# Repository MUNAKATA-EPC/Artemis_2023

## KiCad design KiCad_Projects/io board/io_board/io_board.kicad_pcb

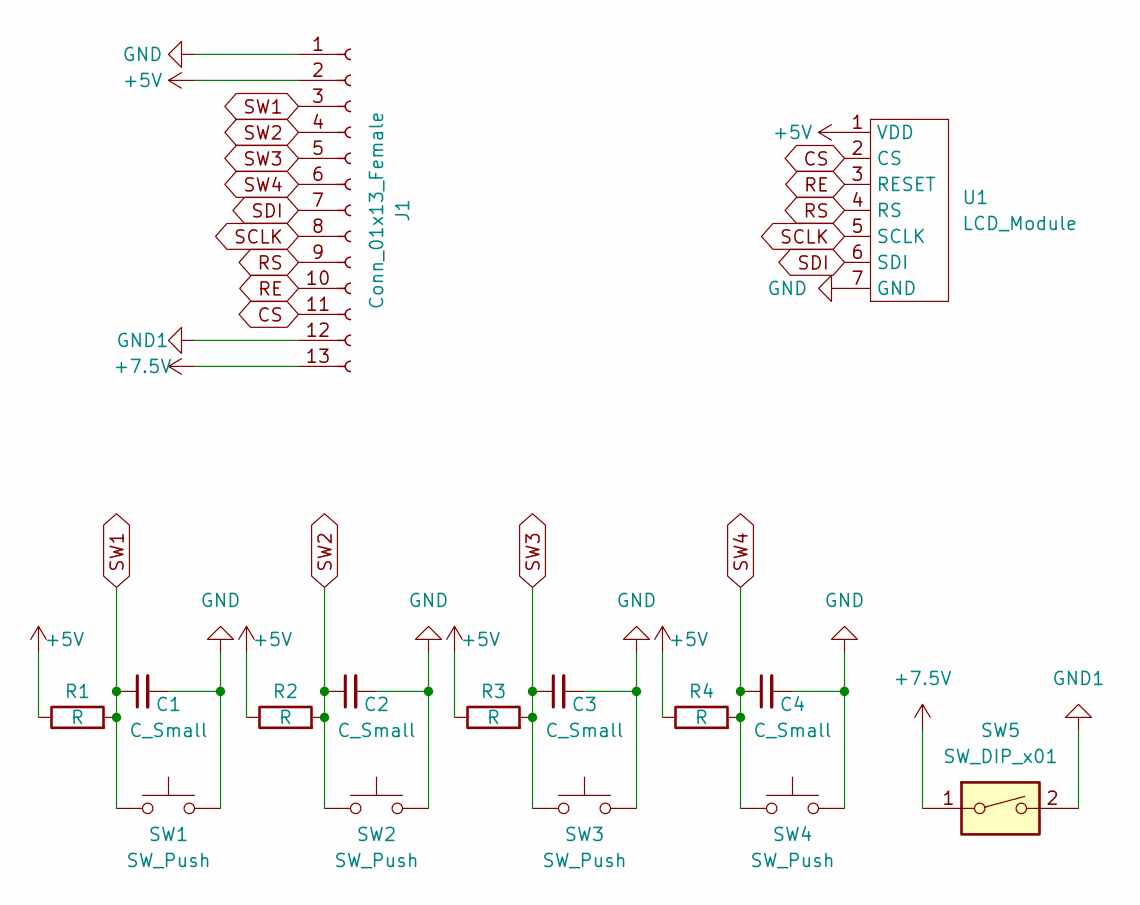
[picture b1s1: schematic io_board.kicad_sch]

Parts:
C1, C2, C3, C4: C_Small
J1: Conn_01x13_Female
R1, R2, R3, R4: R
SW1, SW2, SW3, SW4: SW_Push
SW5: SW_DIP_x01
U1: LCD_Module

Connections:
+5V: J1.2, R1.1, R2.1, R3.1, R4.1, U1.1 (VDD)
+7.5V: J1.13, SW5.1
CS: J1.11, U1.2 (CS)
GND: C1.2, C2.2, C3.2, C4.2, J1.1, SW1.2, SW2.2, SW3.2, SW4.2, U1.7 (GND)
GND1: J1.12, SW5.2
RE: J1.10, U1.3 (RESET)
RS: J1.9, U1.4 (RS)
SCLK: J1.8, U1.5 (SCLK)
SDI: J1.7, U1.6 (SDI)
SW1: C1.1, J1.3, R1.2, SW1.1
SW2: C2.1, J1.4, R2.2, SW2.1
SW3: C3.1, J1.5, R3.2, SW3.1
SW4: C4.1, J1.6, R4.2, SW4.1

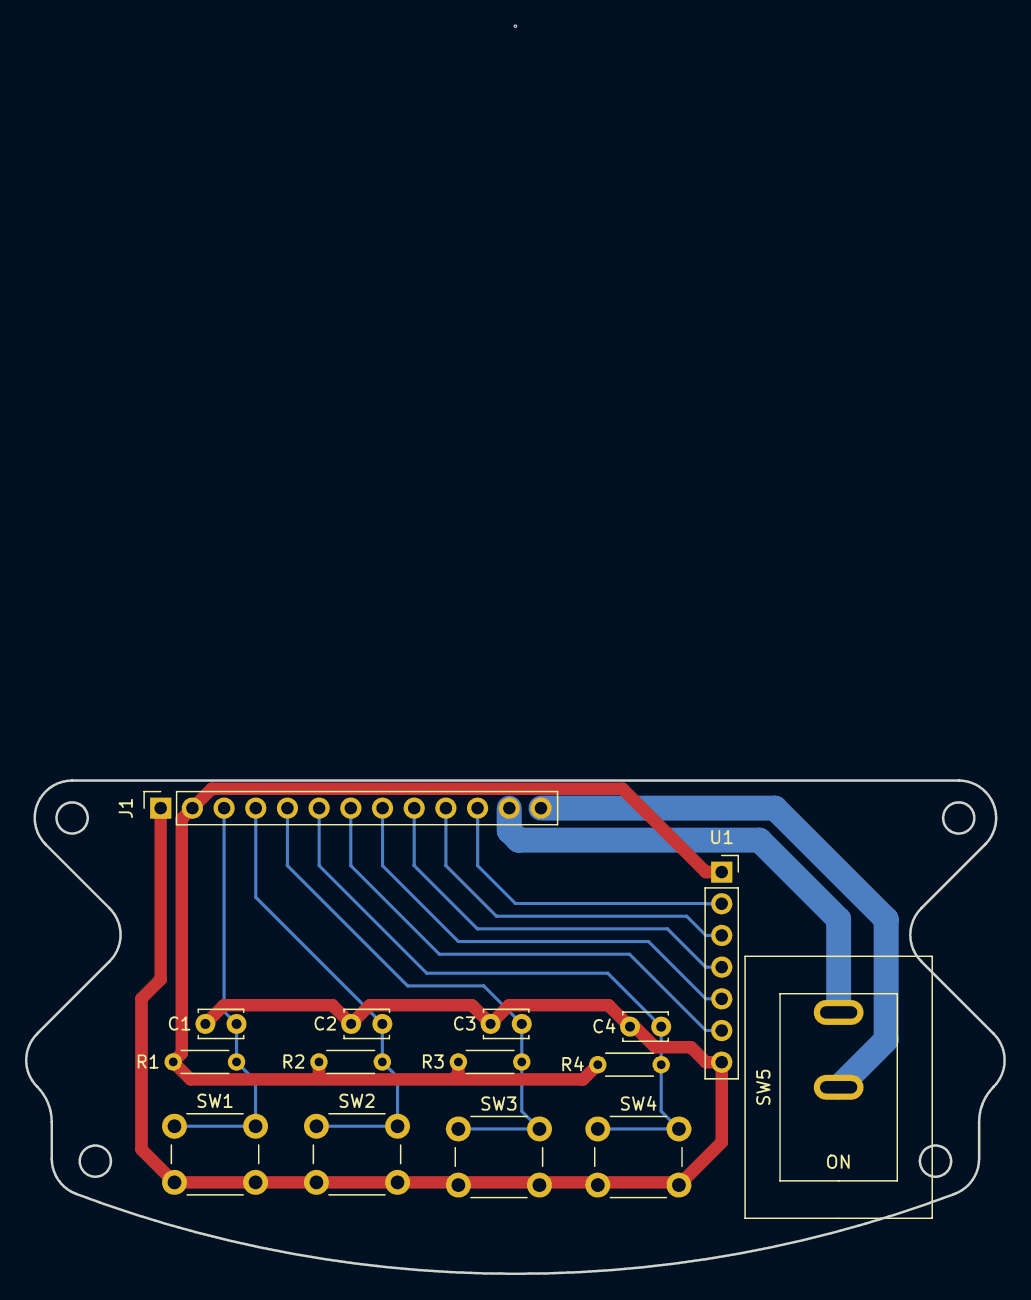
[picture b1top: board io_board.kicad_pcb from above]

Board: 2 copper layers, 78.4 x 39.5 mm, 15 parts (0 on the bottom side), 13 nets.

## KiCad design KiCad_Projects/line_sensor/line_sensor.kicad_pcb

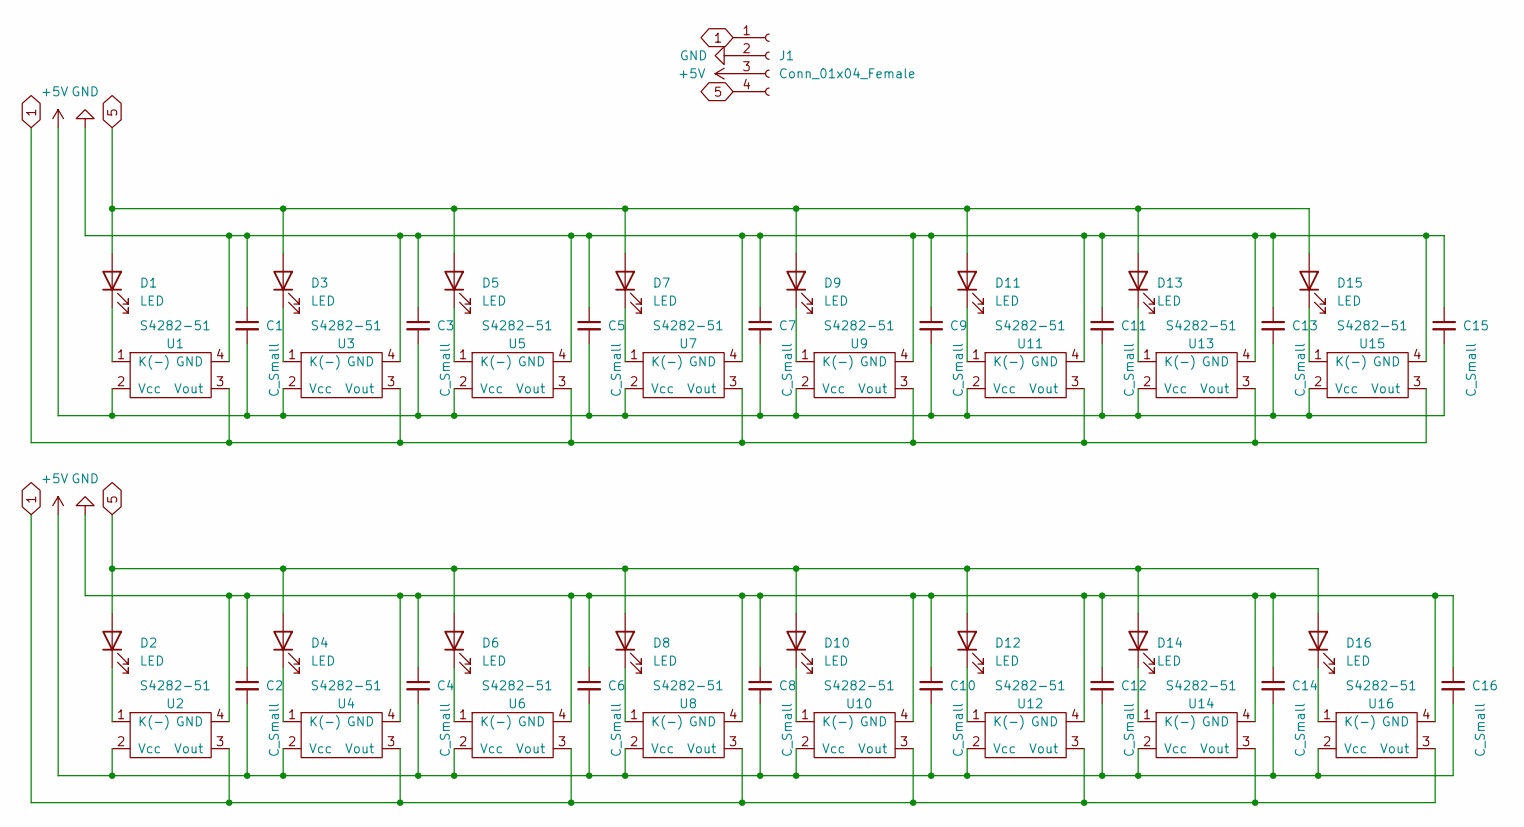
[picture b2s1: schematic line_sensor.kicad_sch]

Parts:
C1, C2, C3, C4, C5, C6, C7, C8, C9, C10, C11, C12, C13, C14, C15, C16: C_Small; C_Disc_D3.8mm_W2.6mm_P2.50mm
D1, D2, D3, D4, D5, D6, D7, D8, D9, D10, D11, D12, D13, D14, D15, D16: LED; LED_D3.0mm_Clear
J1: Conn_01x04_Female; JST_XH_B4B-XH-A_1x04_P2.50mm_Vertical
U1, U2, U3, U4, U5, U6, U7, U8, U9, U10, U11, U12, U13, U14, U15, U16: S4282-51; Line_sennsor

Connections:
1: J1.1, U1.3 (Vout), U2.3 (Vout), U3.3 (Vout), U4.3 (Vout), U5.3 (Vout), U6.3 (Vout), U7.3 (Vout), U8.3 (Vout), U9.3 (Vout), U10.3 (Vout), U11.3 (Vout), U12.3 (Vout), U13.3 (Vout), U14.3 (Vout), U15.3 (Vout), U16.3 (Vout)
5: D1.2 (A), D2.2 (A), D3.2 (A), D4.2 (A), D5.2 (A), D6.2 (A), D7.2 (A), D8.2 (A), D9.2 (A), D10.2 (A), D11.2 (A), D12.2 (A), D13.2 (A), D14.2 (A), D15.2 (A), D16.2 (A), J1.4
+5V: C1.2, C2.2, C3.2, C4.2, C5.2, C6.2, C7.2, C8.2, C9.2, C10.2, C11.2, C12.2, C13.2, C14.2, C15.2, C16.2, J1.3, U1.2 (Vcc), U2.2 (Vcc), U3.2 (Vcc), U4.2 (Vcc), U5.2 (Vcc), U6.2 (Vcc), U7.2 (Vcc), U8.2 (Vcc), U9.2 (Vcc), U10.2 (Vcc), U11.2 (Vcc), U12.2 (Vcc), U13.2 (Vcc), U14.2 (Vcc), U15.2 (Vcc), U16.2 (Vcc)
GND: C1.1, C2.1, C3.1, C4.1, C5.1, C6.1, C7.1, C8.1, C9.1, C10.1, C11.1, C12.1, C13.1, C14.1, C15.1, C16.1, J1.2, U1.4 (GND), U2.4 (GND), U3.4 (GND), U4.4 (GND), U5.4 (GND), U6.4 (GND), U7.4 (GND), U8.4 (GND), U9.4 (GND), U10.4 (GND), U11.4 (GND), U12.4 (GND), U13.4 (GND), U14.4 (GND), U15.4 (GND), U16.4 (GND)
unnamed: D1.1 (K), U1.1 (K(-))
unnamed: D2.1 (K), U2.1 (K(-))
unnamed: D3.1 (K), U3.1 (K(-))
unnamed: D4.1 (K), U4.1 (K(-))
unnamed: D5.1 (K), U5.1 (K(-))
unnamed: D6.1 (K), U6.1 (K(-))
unnamed: D7.1 (K), U7.1 (K(-))
unnamed: D8.1 (K), U8.1 (K(-))
unnamed: D9.1 (K), U9.1 (K(-))
unnamed: D10.1 (K), U10.1 (K(-))
unnamed: D11.1 (K), U11.1 (K(-))
unnamed: D12.1 (K), U12.1 (K(-))
unnamed: D13.1 (K), U13.1 (K(-))
unnamed: D14.1 (K), U14.1 (K(-))
unnamed: D15.1 (K), U15.1 (K(-))
unnamed: D16.1 (K), U16.1 (K(-))

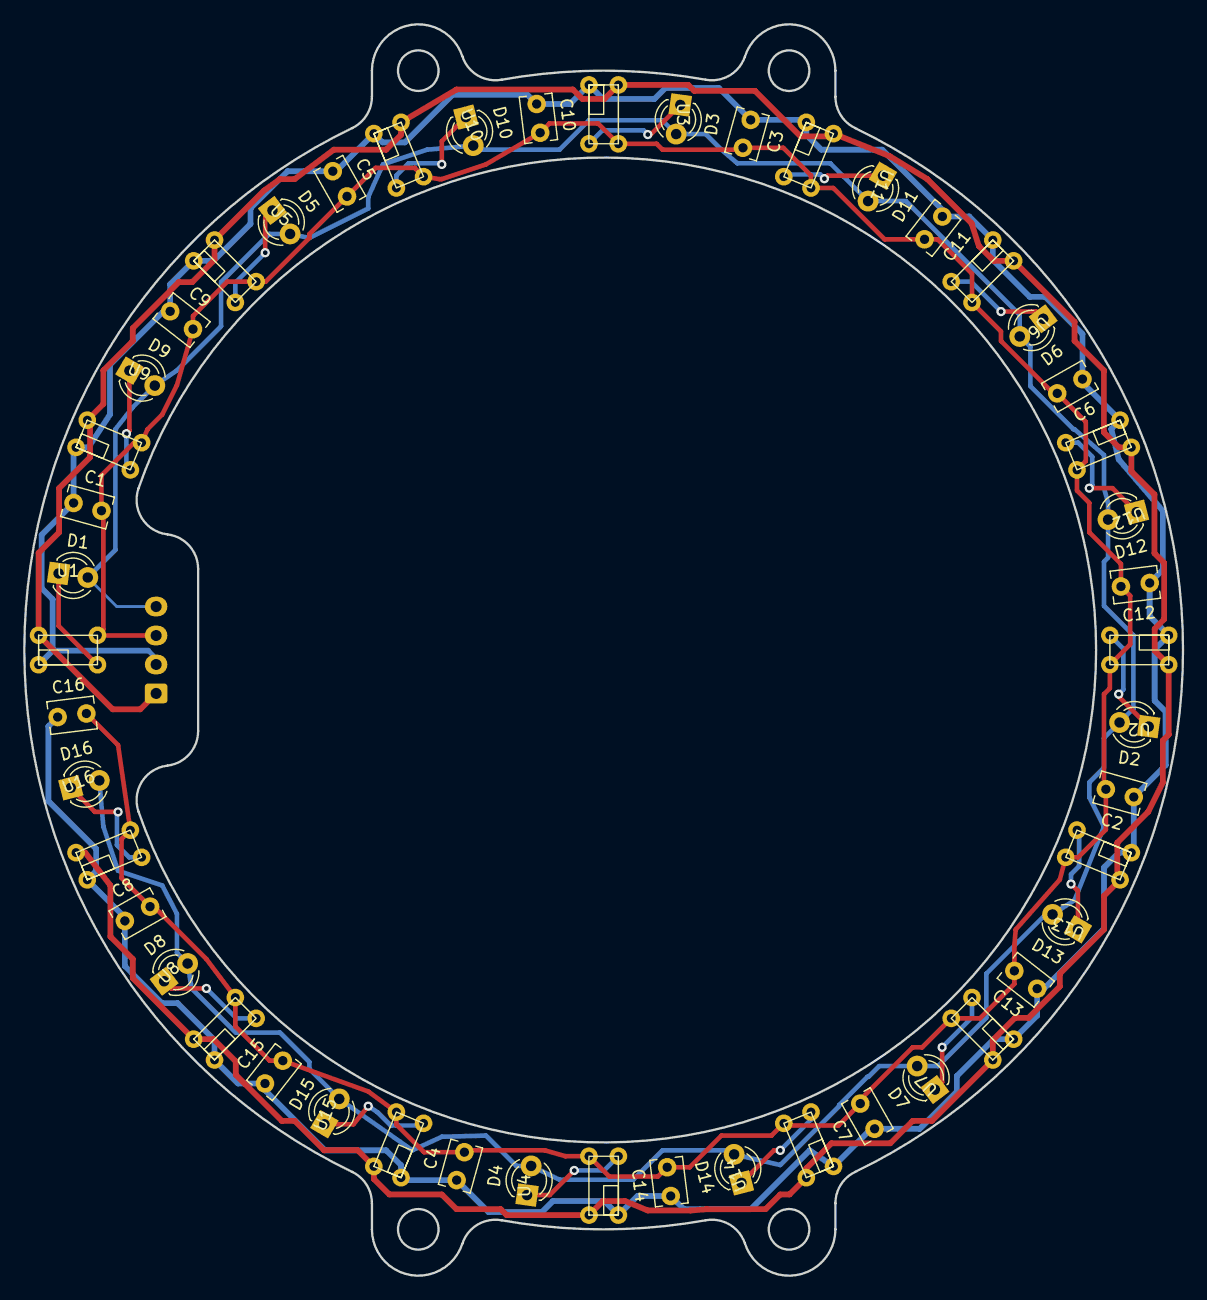
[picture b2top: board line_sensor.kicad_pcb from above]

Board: 2 copper layers, 100.0 x 108.0 mm, 49 parts (1 on the bottom side), 20 nets.

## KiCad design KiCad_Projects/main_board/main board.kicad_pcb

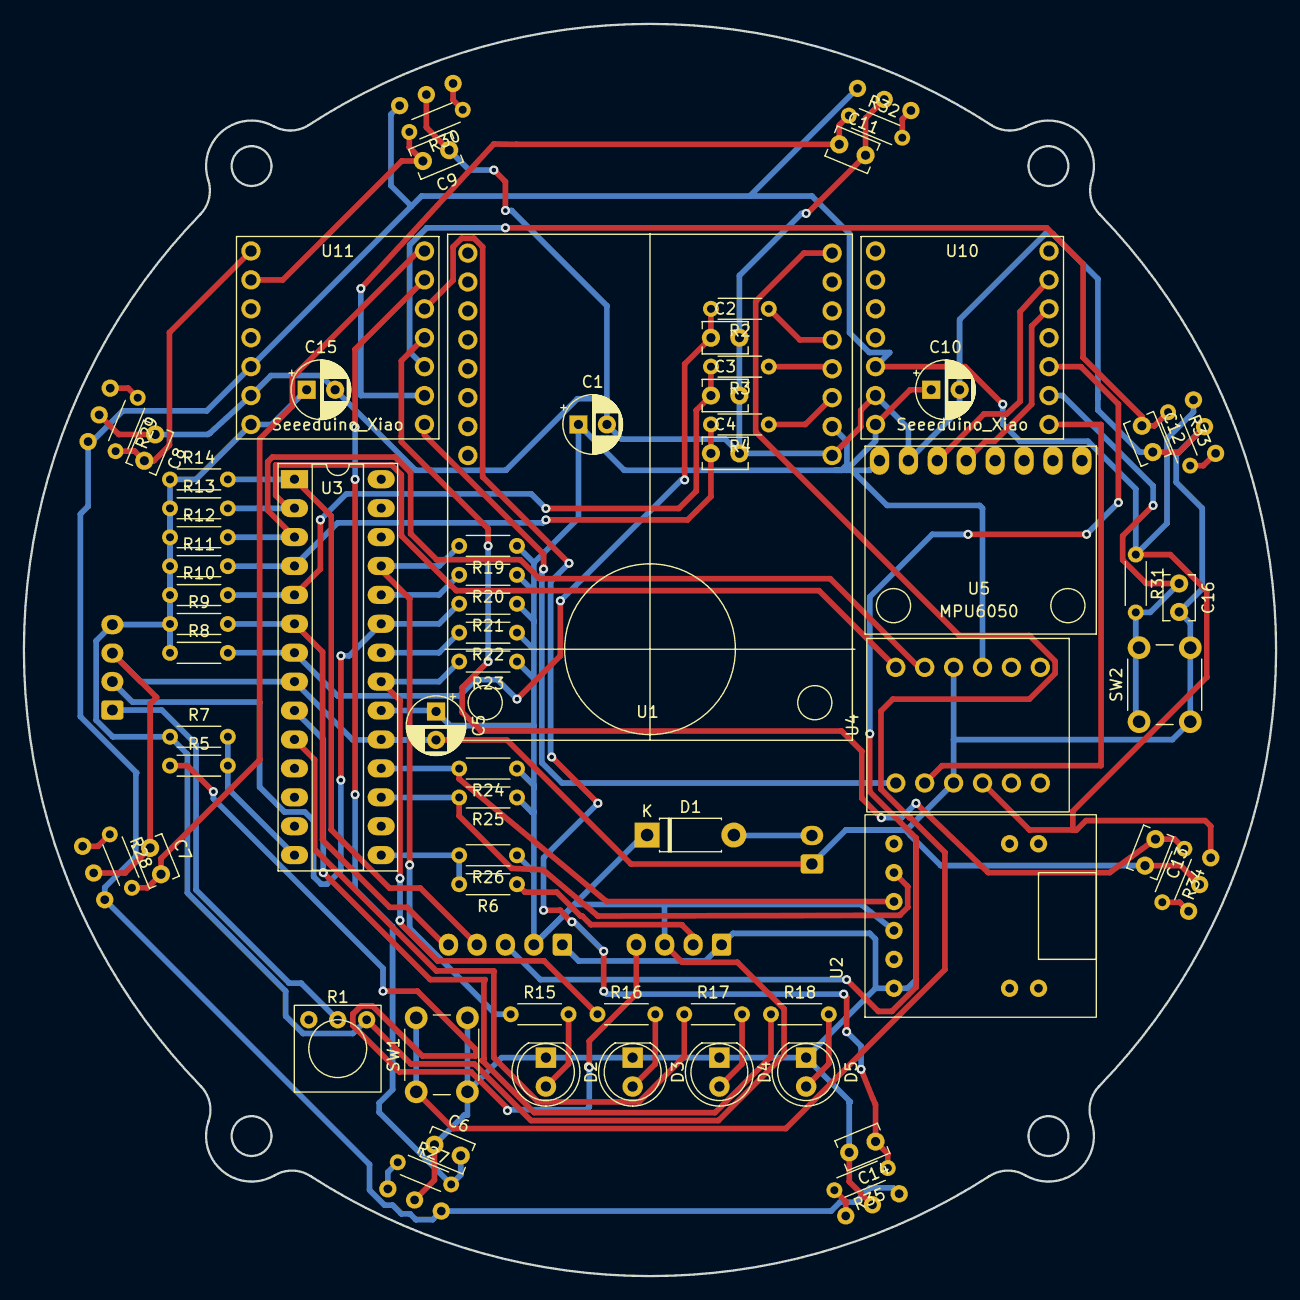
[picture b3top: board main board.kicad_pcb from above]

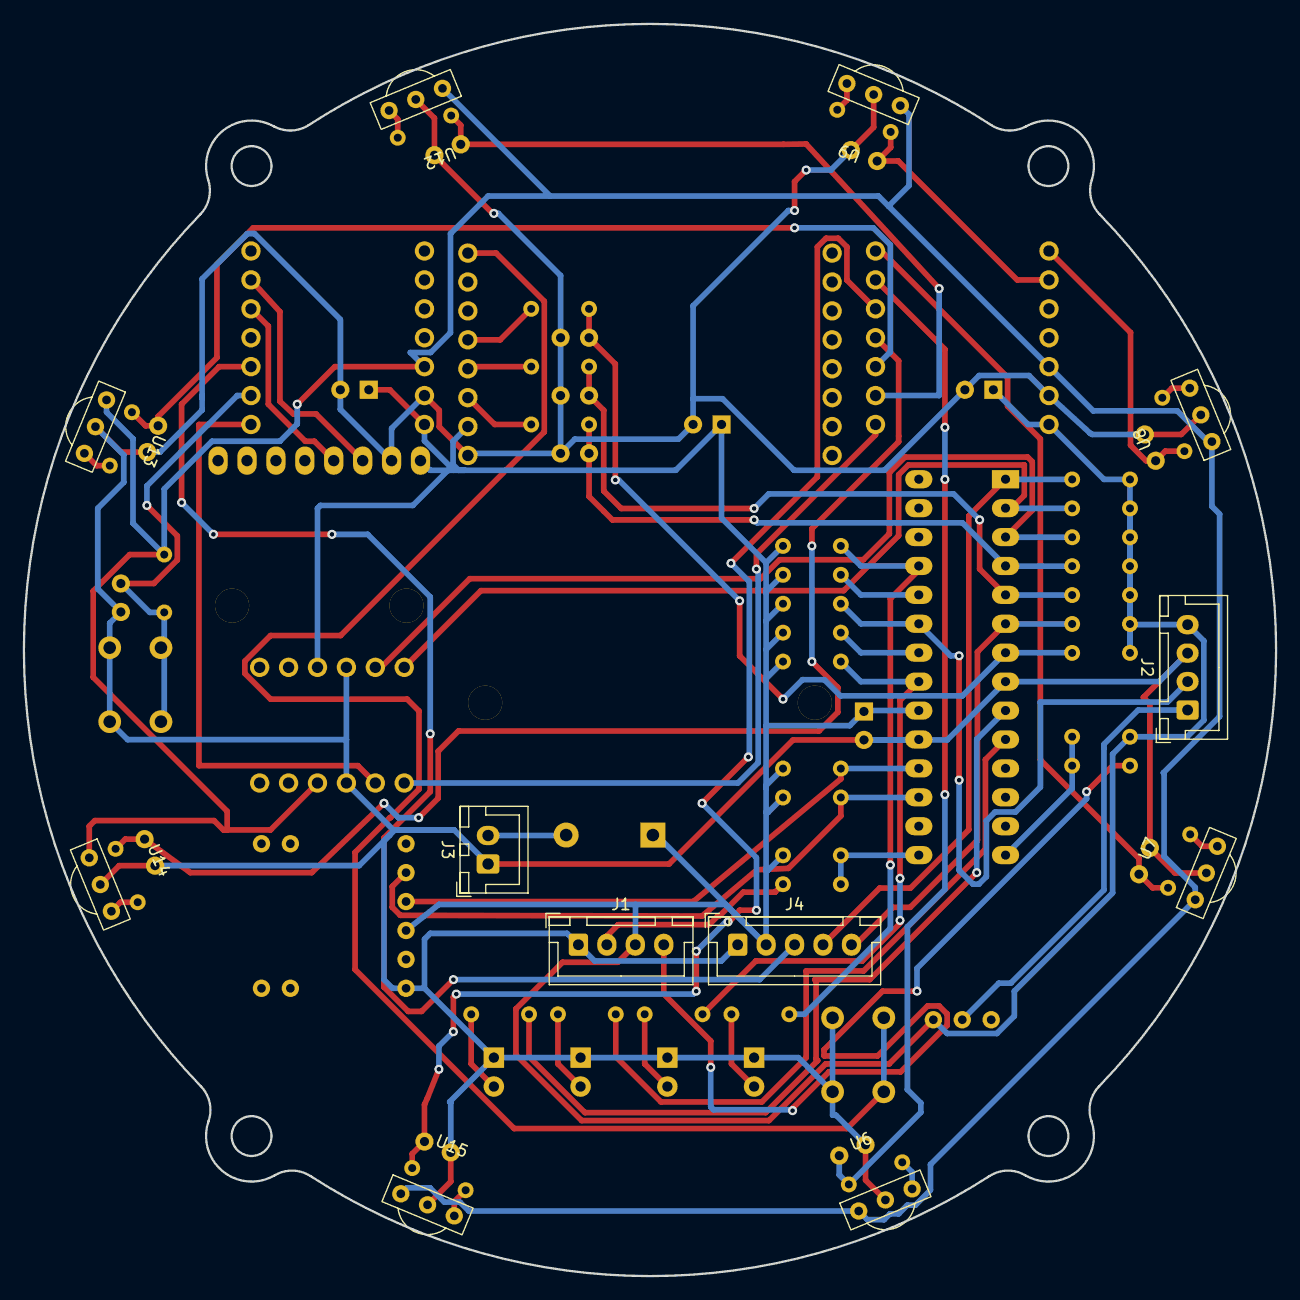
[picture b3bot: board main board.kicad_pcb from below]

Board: 2 copper layers, 110.0 x 110.0 mm, 77 parts (12 on the bottom side), 55 nets.

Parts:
C1, C5, C10, C15: C; CP_Radial_D5.0mm_P2.50mm
C2, C3, C4, C6, C7, C8, C9, C11, C12, C13, C14, C16: C_Small; C_Disc_D3.8mm_W2.6mm_P2.50mm
D1: D; D_DO-41_SOD81_P7.62mm_Horizontal
D2, D3, D4, D5: LED; LED_D5.0mm_Clear
J1, J2: Conn_01x04_Female; JST_XH_B4B-XH-A_1x04_P2.50mm_Vertical
J3: Conn_01x02_Female; JST_XH_B2B-XH-A_1x02_P2.50mm_Vertical
J4: Conn_01x05_Female; JST_XH_B5B-XH-A_1x05_P2.50mm_Vertical
R1: R_Variable; R_Varlable
R2, R3, R4, R31: R; R_Axial_DIN0204_L3.6mm_D1.6mm_P5.08mm_Horizontal
R5, R6, R7, R9, R14, R24, R25, R26: 10k; R_Axial_DIN0204_L3.6mm_D1.6mm_P5.08mm_Horizontal
R8, R10, R11, R12, R13, R19, R20, R21, R22, R23, R27, R28, R29, R30, R32, R33, R34, R35: 100k; R_Axial_DIN0204_L3.6mm_D1.6mm_P5.08mm_Horizontal
R15, R16, R17, R18: 330; R_Axial_DIN0204_L3.6mm_D1.6mm_P5.08mm_Horizontal
SW1, SW2: SW_Push; SW_PUSH_6mm_H5mm
U1: open_mv; OpenMV
U2: type-c_sirial; Type-C_Sirial_Board
U3: PIC18F26K20_ISS; DIP-28_W7.62mm_Socket_LongPads
U4: Akizuki_Logiv_Level_converter; Akizuki_Logic_Level_converter
U5: MPU6050
U6, U7, U8, U9, U12, U13, U14, U15: TSSP58038; TSSP58038_IR
U10, U11: Seeeduino_Xiao; seeeduinoXIAO

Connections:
+3V3: R31.1, U4.9 (LV), U6.2 (Vin), U7.2 (Vin), U8.2 (Vin), U9.2 (Vin), U10.12 (3V3), U11.12 (3V3), U12.2 (Vin), U13.2 (Vin), U14.2 (Vin), U15.2 (Vin)
+5V: C1.1, C5.1, C10.1, C15.1, D1.1 (K), J1.3, J2.4, J4.2, R1.1, R7.1, R8.1, R9.1, R10.1, R11.1, R12.1, R13.1, R14.1, R19.1, R20.1, R21.1, R22.1, R23.1, R24.1, R25.1, R26.1, U1.10 (vin), U2.3 (VCC), U3.20 (Vdd), U4.4 (HV), U5.1 (VCC), U10.14 (5V), U11.14 (5V)
AD1: R13.2, U3.2 (RA0/AN0), U4.1 (HV1)
AD2: R12.2, U3.3 (RA1/AN1), U4.2 (HV2)
AD3: C4.1, R4.2, R11.2, U3.4 (RA2/Vref-AN2)
AD4: C3.1, R3.2, R10.2, U3.5 (RA3/Vref+AN3)
AD5: C2.1, R2.2, R8.2, U3.7 (RA5/AN4)
AD6: J2.2, R21.2, U3.23 (AN8/INT2/RB2)
AD7: R20.2, U3.24 (AN9/RB3)
AD8: R22.2, U3.22 (AN10/INT1/RB1)
AD9: R15.1, R19.2, U3.25 (AN11/RB4)
AD10: R16.1, R23.2, U3.21 (AN12/INT0/RB0)
GND: C1.2, C2.2, C3.2, C4.2, C5.2, C6.1, C7.1, C8.1, C9.1, C10.2, C11.2, C12.2, C13.2, C14.2, C15.2, C16.2, D2.1 (K), D3.1 (K), D4.1 (K), D5.1 (K), J1.1, J2.3, J3.1, J4.1, SW1.2, SW2.2, U1.9 (gnd), U2.1 (GND), U3.8 (Vss), U3.19 (Vss), U4.3 (GND), U4.10 (GND), U5.2 (GND), U6.1 (GND), U7.1 (GND), U8.1 (GND), U9.1 (GND), U10.13 (GND), U11.13 (GND), U12.1 (GND), U13.1 (GND), U14.1 (GND), U15.1 (GND)
IR1: C11.1, R32.1, U11.2
IR2: C12.1, R33.1, U11.3
IR3: C13.1, R34.1, U11.4
IR4: C14.1, R35.1, U11.5 (SDA)
IR5: C6.2, R27.2, U11.6 (SCL)
IR6: C7.2, R28.2, U11.7 (TX)
IR7: C8.2, R29.2, U11.8 (RX)
IR8: C9.2, R30.2, U11.9 (SCK)
LV1: U4.12 (LV1), U11.1 (DAC)
LV2: U4.11 (LV2), U10.1 (DAC)
MCLR: J4.4, R14.2, U3.1 (~MCLR/RE3)
MON LED: R17.1, U3.10 (RA6/OSC2/CLKOUT)
unnamed: D1.2 (A), J3.2
unnamed: D2.2 (A), R15.2
unnamed: D3.2 (A), R16.2
unnamed: D4.2 (A), R17.2
unnamed: D5.2 (A), R18.2
unnamed: J1.2, R6.1
unnamed: J1.4, R5.1
unnamed: J2.1, R1.2
unnamed: R2.1, U1.13 (seru03)
unnamed: R3.1, U1.12 (seru02)
unnamed: R4.1, U1.11 (seru01)
unnamed: SW1.1, U1.16 (rst)
unnamed: R27.1, U6.0 (OUT)
unnamed: R28.1, U7.0 (OUT)
unnamed: R29.1, U8.0 (OUT)
unnamed: R30.1, U9.0 (OUT)
unnamed: U5.4 (SDA), U10.5 (SDA)
unnamed: U5.3 (SCL), U10.6 (SCL)
unnamed: R32.2, U12.0 (OUT)
unnamed: R33.2, U13.0 (OUT)
unnamed: R34.2, U14.0 (OUT)
unnamed: R35.2, U15.0 (OUT)
PWR LED: R18.1, U3.9 (RA7/OSC1/CLKIN)
RA4: J4.5, R9.2, U3.6 (RA4)
RES: C16.1, R31.2, SW2.1, U10.2
RX: R24.2, U2.4 (TXD), U3.18 (RX/RC7)
SCL: R5.2, R7.2, U3.14 (SCL/SCK/RC3)
SDA: R6.2, R26.2, U3.15 (SDA/SDI/RC4)
SW2: J4.3, U10.3
TX: R25.2, U2.5 (RXD), U3.17 (TX/RC6)

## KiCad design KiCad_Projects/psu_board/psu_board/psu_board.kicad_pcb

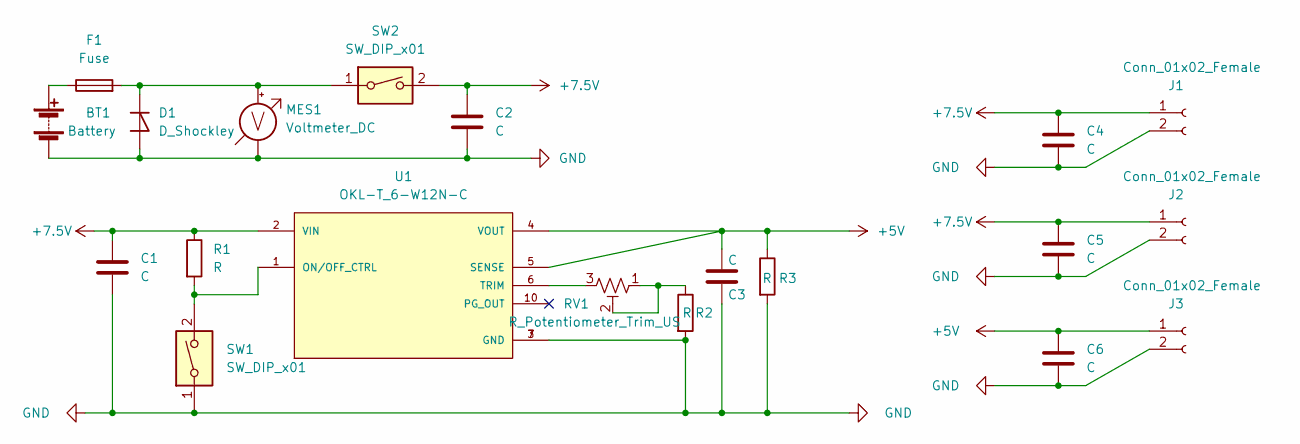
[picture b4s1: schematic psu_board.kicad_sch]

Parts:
BT1: Battery; JST_VH_B2P-VH-B_1x02_P3.96mm_Vertical
C1, C3, C6: C; C_Disc_D3.8mm_W2.6mm_P2.50mm
C2, C4, C5: C; CP_Radial_D5.0mm_P2.50mm
D1: D_Shockley; D_5W_P10.16mm_Horizontal
F1: Fuse; fuse_socket
J1, J2, J3: Conn_01x02_Female; JST_XH_B2B-XH-A_1x02_P2.50mm_Vertical
MES1: Voltmeter_DC; voltage_counter
R1, R2, R3: R; R_Axial_DIN0204_L3.6mm_D1.6mm_P5.08mm_Horizontal
RV1: R_Potentiometer_Trim_US; Potentiometer_Bourns_3296W_Vertical
SW1: SW_DIP_x01; 2MS1T2B4M2QES
SW2: SW_DIP_x01; DS-850k
U1: OKL-T_6-W12N-C; DCDC-murata-6A

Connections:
+5V: C3.1, C6.1, J3.1, R3.1, U1.4 (VOUT), U1.5 (SENSE)
+7.5V: C1.1, C2.1, C4.1, C5.1, J1.1, J2.1, R1.1, SW2.2, U1.2 (VIN)
GND: BT1.2 (-), C1.2, C2.2, C3.2, C4.2, C5.2, C6.2, D1.2 (A), J1.2, J2.2, J3.2, MES1.1 (-), R2.2, R3.2, SW1.1, U1.3 (GND), U1.7 (GND)
unnamed: BT1.1 (+), F1.1
unnamed: D1.1 (K), F1.2, MES1.2 (+), SW2.1
unnamed: R1.2, SW1.2, U1.1 (ON/OFF_CTRL)
unnamed: R2.1, RV1.1, RV1.2
unnamed: RV1.3, U1.6 (TRIM)

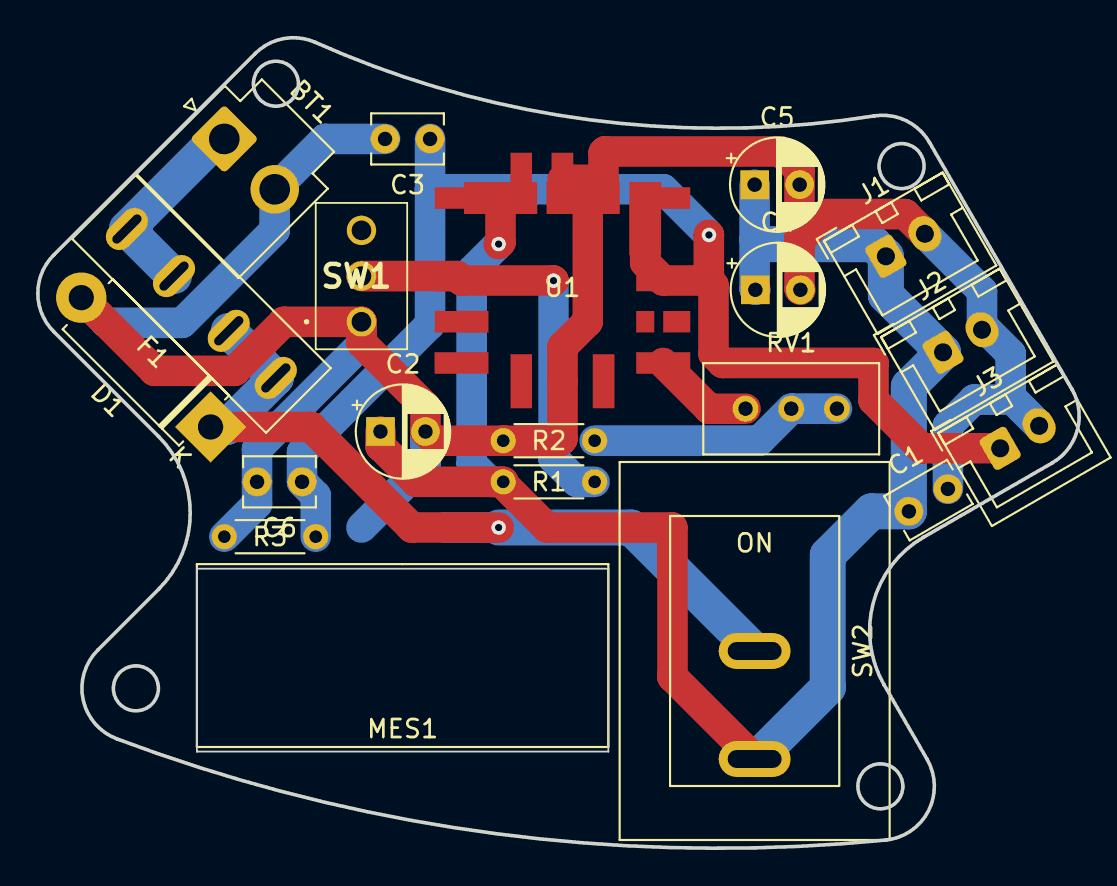
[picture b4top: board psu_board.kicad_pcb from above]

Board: 2 copper layers, 57.9 x 45.0 mm, 20 parts (0 on the bottom side), 8 nets.

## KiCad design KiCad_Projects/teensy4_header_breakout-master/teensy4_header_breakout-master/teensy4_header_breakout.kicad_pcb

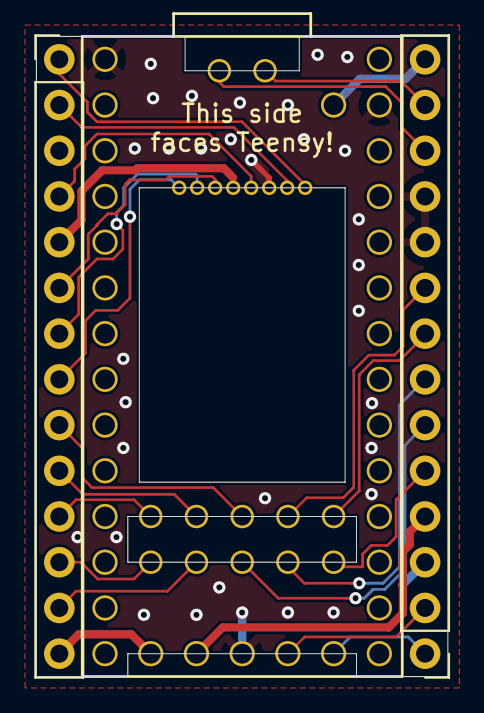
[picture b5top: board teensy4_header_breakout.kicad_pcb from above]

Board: 2 copper layers, 22.9 x 35.6 mm, 3 parts (0 on the bottom side), 25 nets.

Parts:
J1, J2: Conn_01x14; PinHeader_1x14_P2.54mm_Vertical
U1: GND-1; Teensy40_SMT

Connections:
/3V3-1: J2.4, U1.16
/3V3-SD: J1.5, U1.49
/24: J2.5, U1.35
/25: J2.8, U1.36
/26: J2.7, U1.37
/27: J2.9, U1.38
/28: J2.6, U1.39
/29: J1.9, U1.40
/30: J1.13, U1.41
/31: J1.10, U1.42
/32: J1.12, U1.43
/33: J1.11, U1.44
/CLK: J1.4, U1.48
/CMD: J1.6, U1.50
/D+: J2.12, U1.54
/D-: J2.13, U1.53
/DAT0: J1.2, U1.46
/DAT1: J1.1, U1.45
/DAT2: J1.8, U1.52
/DAT3: J1.7, U1.51
/GND: J1.3, J2.3, J2.10, J2.11, U1.1, U1.17, U1.32, U1.47
/ON_OFF: J2.1, U1.19
/PROGRAM: J2.2, U1.18
/VBAT: J1.14, U1.15
/VUSB: J2.14, U1.34

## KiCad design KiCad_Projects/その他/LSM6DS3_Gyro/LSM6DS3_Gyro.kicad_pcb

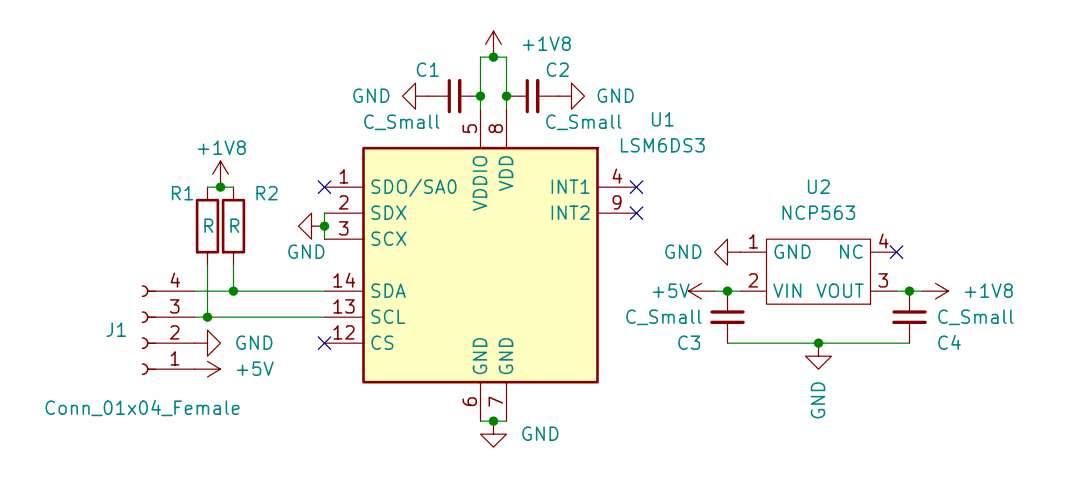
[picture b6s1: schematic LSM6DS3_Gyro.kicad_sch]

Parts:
C1, C2, C3, C4: C_Small; C_0201_0603Metric
J1: Conn_01x04_Female; PinHeader_1x04_P2.54mm_Vertical
R1, R2: R; R_0201_0603Metric
U1: LSM6DS3; LGA-14_3x2.5mm_P0.5mm_LayoutBorder3x4y
U2: NCP563

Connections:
+1V8: C1.2, C2.1, C4.1, R1.1, R2.1, U1.5 (VDDIO), U1.8 (VDD), U2.3 (VOUT)
+5V: C3.1, J1.1, U2.2 (VIN)
GND: C1.1, C2.2, C3.2, C4.2, J1.2, U1.2 (SDX), U1.3 (SCX), U1.6 (GND), U1.7 (GND), U2.1 (GND)
unnamed: J1.3, R1.2, U1.13 (SCL)
unnamed: J1.4, R2.2, U1.14 (SDA)

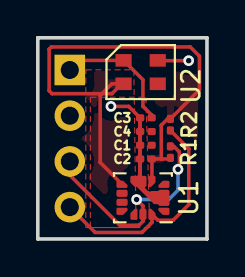
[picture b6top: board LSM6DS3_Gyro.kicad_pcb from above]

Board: 2 copper layers, 9.4 x 11.2 mm, 9 parts (1 on the bottom side), 5 nets.

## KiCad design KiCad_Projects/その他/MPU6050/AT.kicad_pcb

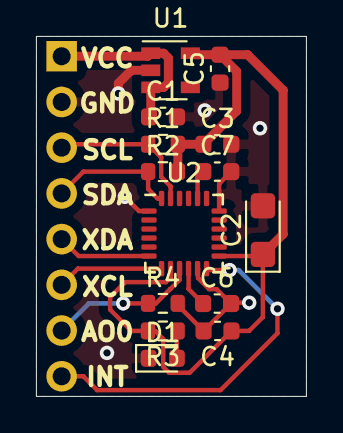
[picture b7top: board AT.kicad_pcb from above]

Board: 2 copper layers, 15.0 x 20.0 mm, 15 parts (1 on the bottom side), 12 nets.

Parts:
C1, C3, C4, C5, C6, C7: C_Small; C_0603_1608Metric
C2: C_Small; CP_EIA-3216-10_Kemet-I
D1: LED; LED_0603_1608Metric
J1: Conn_01x08; PinHeader_1x08_P2.54mm_Vertical
R1, R2, R3, R4: R_Small; R_0603_1608Metric
U1: TLV713185PDBV; SOT-23-5
U2: MPU-6050; InvenSense_QFN-24_4x4mm_P0.5mm

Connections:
+3V3: C2.1, C3.1, C4.1, C5.2, R1.2, R2.2, R3.2, U1.5, U2.8, U2.13
+5V: C1.1, J1.1, U1.1, U1.3
/AD0: J1.7, R4.1, U2.9
/INT: J1.8, U2.12
/SCL: J1.3, R1.1, U2.23
/SDA: J1.4, R2.1, U2.24
/XCL: J1.6, U2.7
/XDA: J1.5, U2.6
GND: C1.2, C2.2, C3.2, C4.2, C5.1, C6.2, C7.2, D1.1, J1.2, R4.2, U1.2, U2.1, U2.11, U2.18
unnamed: C6.1, U2.10
unnamed: C7.1, U2.20
unnamed: D1.2, R3.1

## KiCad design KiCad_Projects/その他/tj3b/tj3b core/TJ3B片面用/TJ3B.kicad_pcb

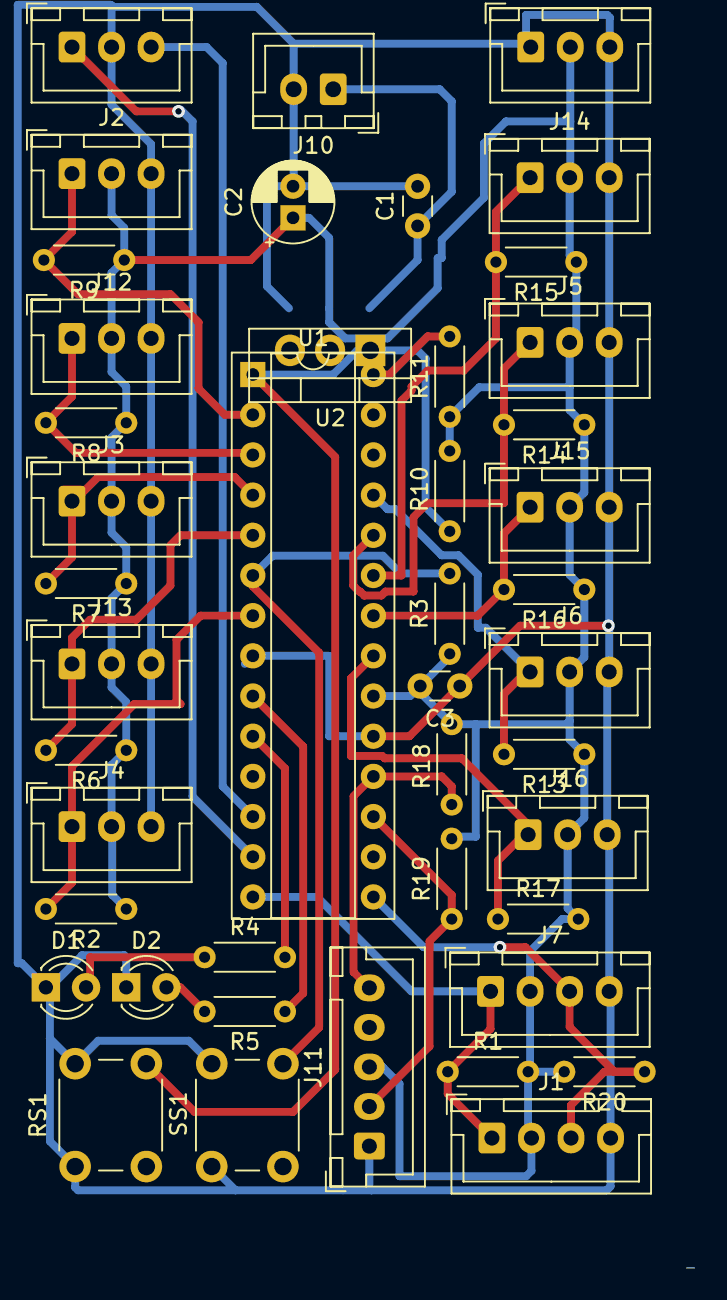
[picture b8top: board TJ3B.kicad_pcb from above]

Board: 2 copper layers, 44 parts (0 on the bottom side), 26 nets.

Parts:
C1, C3: C; C_Disc_D3.0mm_W1.6mm_P2.50mm
C2: C; CP_Radial_D5.0mm_P2.00mm
D1, D2: LED; LED_D3.0mm
J1, J7: Conn_01x04_Female; JST_XH_B4B-XH-A_1x04_P2.50mm_Vertical
J2, J3, J4, J5, J6, J8, J9, J12, J13, J14, J15, J16: Conn_01x03_Female; JST_XH_B3B-XH-A_1x03_P2.50mm_Vertical
J10: Conn_01x02_Female; JST_XH_B2B-XH-A_1x02_P2.50mm_Vertical
J11: Conn_01x05_Female; JST_XH_B5B-XH-A_1x05_P2.50mm_Vertical
R1, R2, R3, R4, R5, R6, R7, R8, R9, R10, R13, R14, R15, R16, R17, R18, R19, R20: R; R_Axial_DIN0204_L3.6mm_D1.6mm_P5.08mm_Horizontal
R11: 100kΩ; R_Axial_DIN0204_L3.6mm_D1.6mm_P5.08mm_Horizontal
RS1: SW_Push; SW_PUSH_6mm
SS1: SW_Push; SW_PUSH_6mm
U1: TJ3_mein; DIP-28_W7.62mm_Socket
U2: L7805; TO-220-3_Vertical

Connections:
+5V: C2.1, C3.2, J1.2, J2.2, J3.2, J4.2, J5.2, J6.2, J7.2, J8.2, J11.3, J12.2, J13.2, J14.2, J15.2, J16.2, R1.2, R2.1, R3.1, R6.1, R7.1, R8.1, R9.1, R10.2, R11.1, R13.1, R14.1, R15.1, R16.1, R17.2, R18.1, R19.2, R20.2, U1.20, U2.3
AD1: J2.1, R9.2, U1.2
AD2: J12.1, R8.2, U1.3
AD3: J3.1, R7.2, U1.4
AD4: J13.1, R6.2, U1.5
AD5: J4.1, R2.2, U1.7
AD6: J14.1, R15.2, U1.23
AD7: J5.1, R14.2, U1.24
AD8: J15.1, R16.2, U1.22
AD9: J6.1, R13.2, U1.25
AD10: J16.1, R17.1, U1.21
GND: C1.2, C2.2, C3.1, D1.1, D2.1, J1.4, J2.3, J3.3, J4.3, J5.3, J6.3, J7.4, J8.1, J8.3, J9.2, J10.2, J11.1, J12.3, J13.3, J14.3, J15.3, J16.3, RS1.2, SS1.2, U1.8, U1.19, U2.2
MCLR: R10.1, RS1.1, U1.1
MON_LED: R4.2, U1.10
unnamed: C1.1, J10.1, U2.1
unnamed: D1.2, R4.1
unnamed: D2.2, R5.1
PGD_×: R11.2, U1.28
PWM1: J9.3, U1.12
PWM2: J9.1, U1.13
PWR_LED: R5.2, U1.9
RA4: R3.2, SS1.1, U1.6
RX: J11.5, R18.2, U1.18
SCL: J1.1, J7.1, R1.1, U1.14
SDA: J1.3, J7.3, R20.1, U1.15
TX: J11.2, R19.1, U1.17
